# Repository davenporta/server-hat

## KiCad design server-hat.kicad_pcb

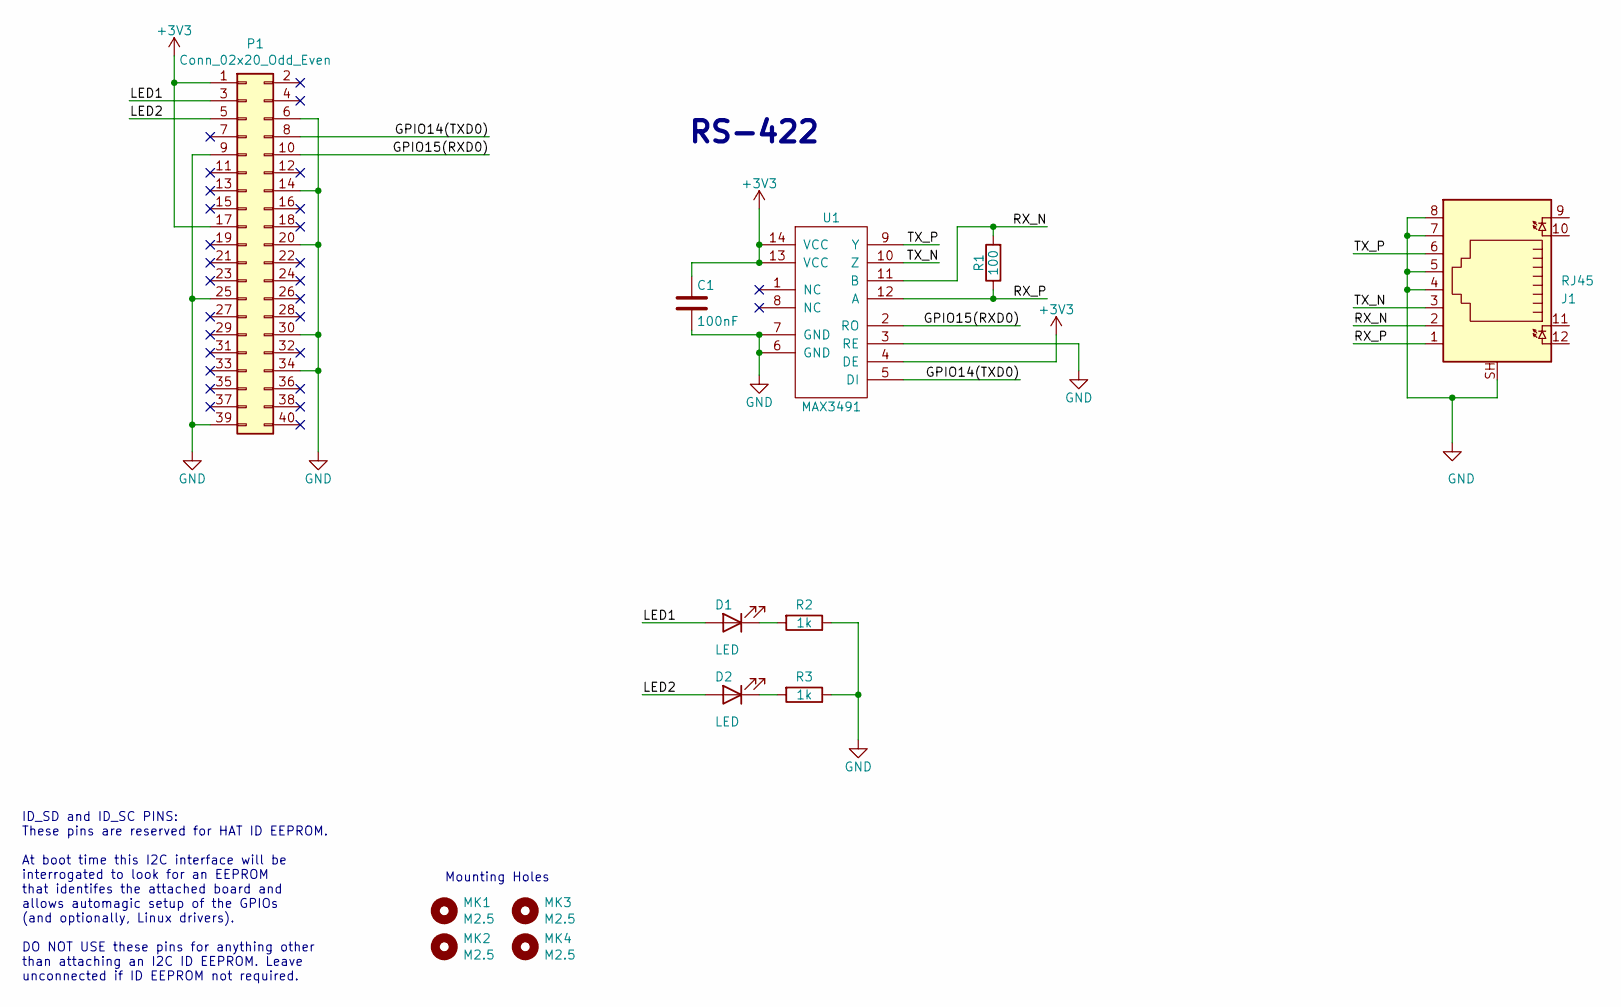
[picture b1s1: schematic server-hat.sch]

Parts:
C1: 100nF; C_0603_1608Metric
D1, D2: LED; LED_0603_1608Metric
J1: RJ45; RJ45_Amphenol_RJHSE538X
MK1, MK2, MK3, MK4: M2.5; MountingHole_2.7mm_M2.5
P1: Conn_02x20_Odd_Even; PinSocket_2x20_P2.54mm_Vertical
R1: 100; R_0603_1608Metric
R2, R3: 1k; R_0603_1608Metric
U1: MAX3491; SOIC-14_3.9x8.7mm_P1.27mm

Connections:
+3V3: C1.1, P1.1, P1.17, U1.4 (DE), U1.13 (VCC), U1.14 (VCC)
/GPIO14(TXD0): P1.8, U1.5 (DI)
/GPIO15(RXD0): P1.10, U1.2 (RO)
/LED1: D1.2 (A), P1.3
/LED2: D2.2 (A), P1.5
/RX_N: J1.2, R1.2, U1.11 (B)
/RX_P: J1.1, R1.1, U1.12 (A)
/TX_N: J1.3, U1.10 (Z)
/TX_P: J1.6, U1.9 (Y)
GND: C1.2, J1.4, J1.5, J1.7, J1.8, J1.SH, P1.6, P1.9, P1.14, P1.20, P1.25, P1.30, P1.34, P1.39, R2.1, R3.1, U1.3 (RE), U1.6 (GND), U1.7 (GND)
unnamed: D1.1 (K), R2.2
unnamed: D2.1 (K), R3.2

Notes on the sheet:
ID_SD and ID_SC PINS: These pins are reserved for HAT ID EEPROM. At boot time this I2C interface will be interrogated to look for an EEPROM that identifes the attached board and allows automagic setup of the GPIOs (and optionally, Linux drivers). DO NOT USE these pins for anything other than attach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
Mounting Holes
RS-422

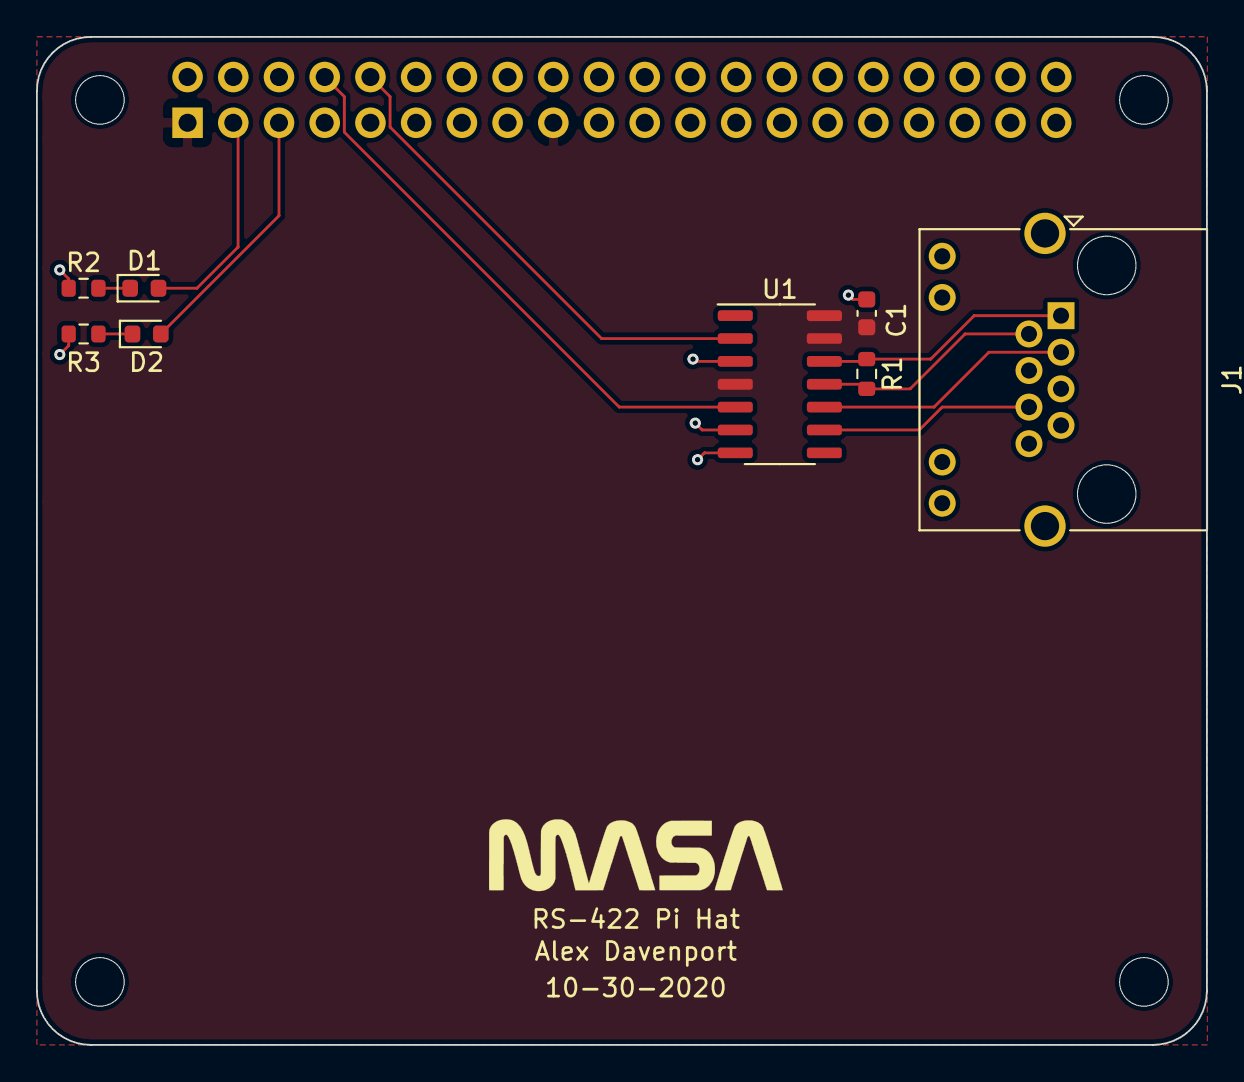
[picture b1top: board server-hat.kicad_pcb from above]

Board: 2 copper layers, 65.0 x 56.0 mm, 13 parts (1 on the bottom side), 12 nets.

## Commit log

2021-07-20 fabbed and tested
